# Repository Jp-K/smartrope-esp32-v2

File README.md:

# A-New-RoPE
Repository for testing the new version of RoPE's firmware

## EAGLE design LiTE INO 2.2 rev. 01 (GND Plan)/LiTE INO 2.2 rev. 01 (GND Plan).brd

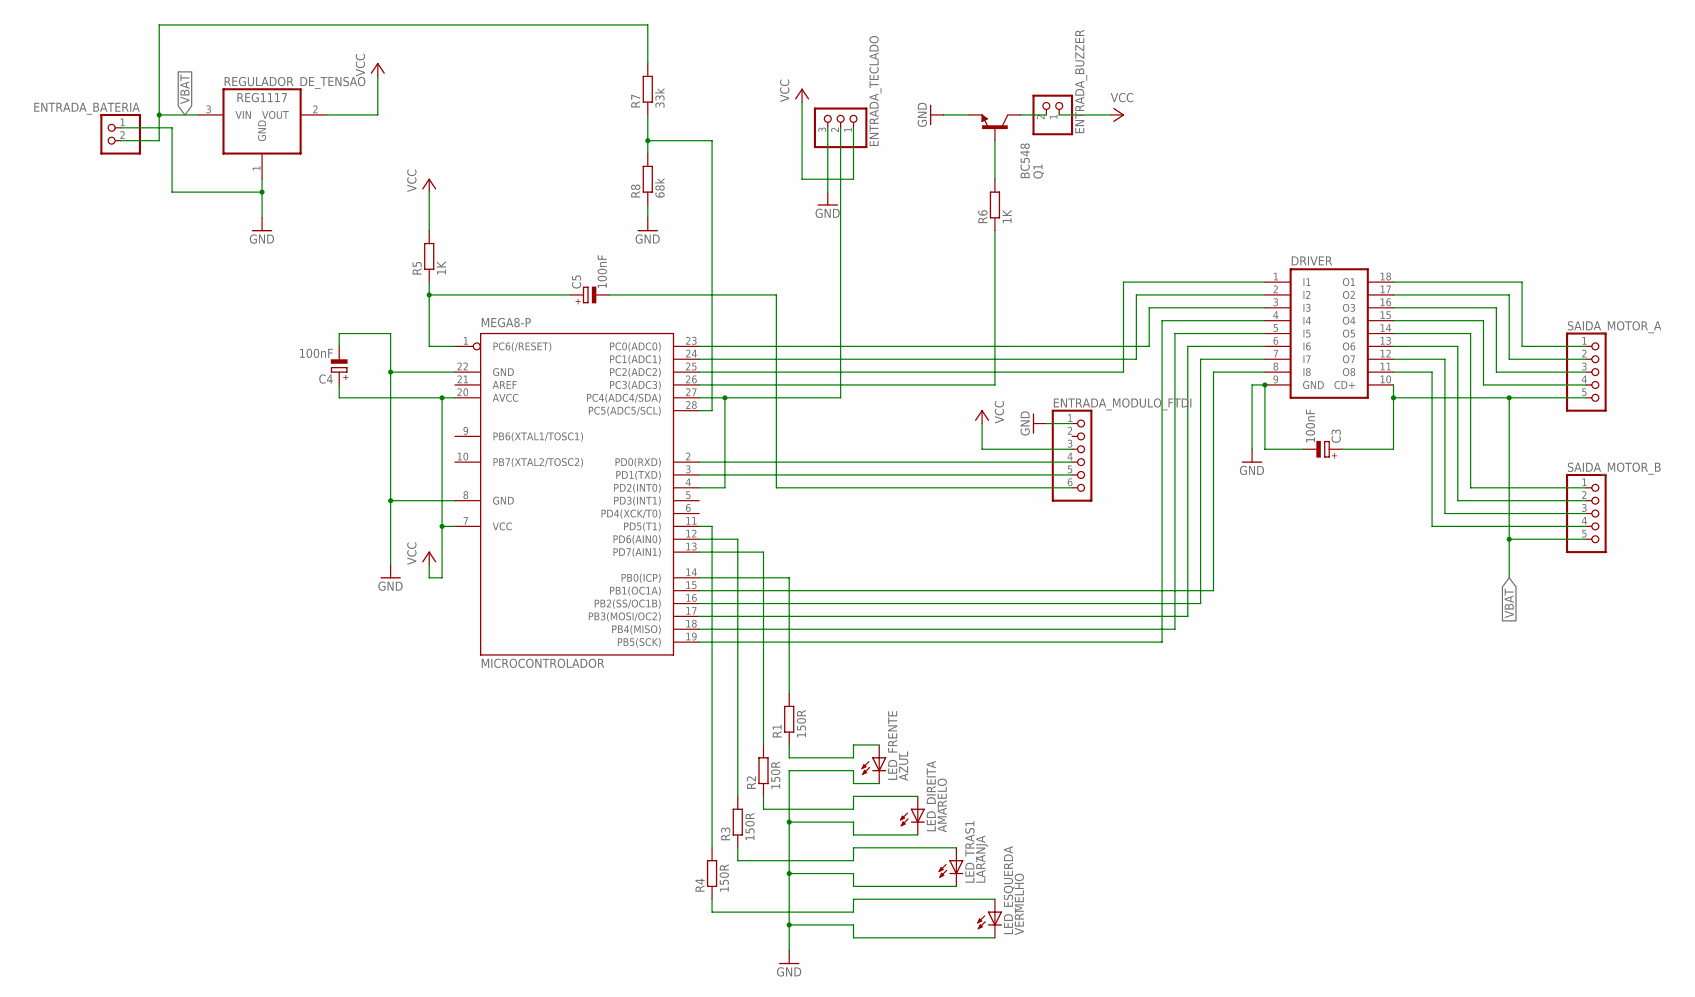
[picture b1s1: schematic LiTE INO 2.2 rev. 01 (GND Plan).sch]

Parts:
C3, C4, C5: 100nF; E5-5
DRIVER: ULN2803A; DIL18
ENTRADA_BATERIA: PINHD-1X2/90; 1X02/90
ENTRADA_BUZZER: PINHD-1X2/90; 1X02/90
ENTRADA_MODULO_FTDI: PINHD-1X6/90; 1X06/90
ENTRADA_TECLADO: PINHD-1X3/90; 1X03/90
LED_DIREITA: AMARELO; LED5MM
LED_ESQUERDA: VERMELHO; LED5MM
LED_FRENTE: AZUL; LED5MM
LED_TRAS1: LARANJA; LED5MM
MICROCONTROLADOR: MEGA8-P; DIL28-3
Q1: BC548; TO92-EBC
R1, R2, R3, R4: 150R; 0204/7
R5, R6: 1K; 0204/7
R7: 33k; 0204/7
R8: 68k; 0204/7
REGULADOR_DE_TENSAO: REG1117; SOT223
SAIDA_MOTOR_A: PINHD-1X5/90; 1X05/90
SAIDA_MOTOR_B: PINHD-1X5/90; 1X05/90

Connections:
GND: C3.-, C4.-, DRIVER.9 (GND), ENTRADA_BATERIA.1, ENTRADA_MODULO_FTDI.1, ENTRADA_TECLADO.3, LED_DIREITA.K (C), LED_ESQUERDA.K (C), LED_FRENTE.K (C), LED_TRAS1.K (C), MICROCONTROLADOR.8 (GND), MICROCONTROLADOR.22 (GND), Q1.E, R8.1, REGULADOR_DE_TENSAO.1 (GND)
unnamed: DRIVER.1 (I1), MICROCONTROLADOR.25 (PC2(ADC2))
unnamed: DRIVER.2 (I2), MICROCONTROLADOR.24 (PC1(ADC1))
unnamed: DRIVER.3 (I3), MICROCONTROLADOR.23 (PC0(ADC0))
unnamed: DRIVER.4 (I4), MICROCONTROLADOR.19 (PB5(SCK))
unnamed: DRIVER.5 (I5), MICROCONTROLADOR.18 (PB4(MISO))
unnamed: DRIVER.6 (I6), MICROCONTROLADOR.17 (PB3(MOSI/OC2))
unnamed: DRIVER.7 (I7), MICROCONTROLADOR.16 (PB2(SS/OC1B))
unnamed: DRIVER.8 (I8), MICROCONTROLADOR.15 (PB1(OC1A))
unnamed: LED_FRENTE.A, R1.1
unnamed: DRIVER.18 (O1), SAIDA_MOTOR_A.1
unnamed: DRIVER.17 (O2), SAIDA_MOTOR_A.2
unnamed: DRIVER.16 (O3), SAIDA_MOTOR_A.3
unnamed: DRIVER.15 (O4), SAIDA_MOTOR_A.4
unnamed: LED_DIREITA.A, R2.1
unnamed: DRIVER.14 (O5), SAIDA_MOTOR_B.1
unnamed: DRIVER.13 (O6), SAIDA_MOTOR_B.2
unnamed: DRIVER.12 (O7), SAIDA_MOTOR_B.3
unnamed: DRIVER.11 (O8), SAIDA_MOTOR_B.4
unnamed: LED_TRAS1.A, R3.1
unnamed: MICROCONTROLADOR.14 (PB0(ICP)), R1.2
unnamed: MICROCONTROLADOR.13 (PD7(AIN1)), R2.2
unnamed: MICROCONTROLADOR.12 (PD6(AIN0)), R3.2
unnamed: MICROCONTROLADOR.11 (PD5(T1)), R4.2
unnamed: ENTRADA_TECLADO.2, MICROCONTROLADOR.4 (PD2(INT0)), MICROCONTROLADOR.27 (PC4(ADC4/SDA))
unnamed: ENTRADA_BUZZER.2, Q1.C
unnamed: MICROCONTROLADOR.28 (PC5(ADC5/SCL)), R7.1, R8.2
unnamed: LED_ESQUERDA.A, R4.1
unnamed: MICROCONTROLADOR.26 (PC3(ADC3)), R6.1
unnamed: ENTRADA_MODULO_FTDI.4, MICROCONTROLADOR.2 (PD0(RXD))
unnamed: ENTRADA_MODULO_FTDI.5, MICROCONTROLADOR.3 (PD1(TXD))
unnamed: C5.-, ENTRADA_MODULO_FTDI.6
unnamed: C5.+, MICROCONTROLADOR.1 (PC6(/RESET)), R5.1
unnamed: Q1.B, R6.2
VBAT: C3.+, DRIVER.10 (CD+), ENTRADA_BATERIA.2, R7.2, REGULADOR_DE_TENSAO.3 (VIN), SAIDA_MOTOR_A.5, SAIDA_MOTOR_B.5
VCC: C4.+, ENTRADA_BUZZER.1, ENTRADA_MODULO_FTDI.3, ENTRADA_TECLADO.1, MICROCONTROLADOR.7 (VCC), MICROCONTROLADOR.20 (AVCC), R5.2, REGULADOR_DE_TENSAO.2 (VOUT)

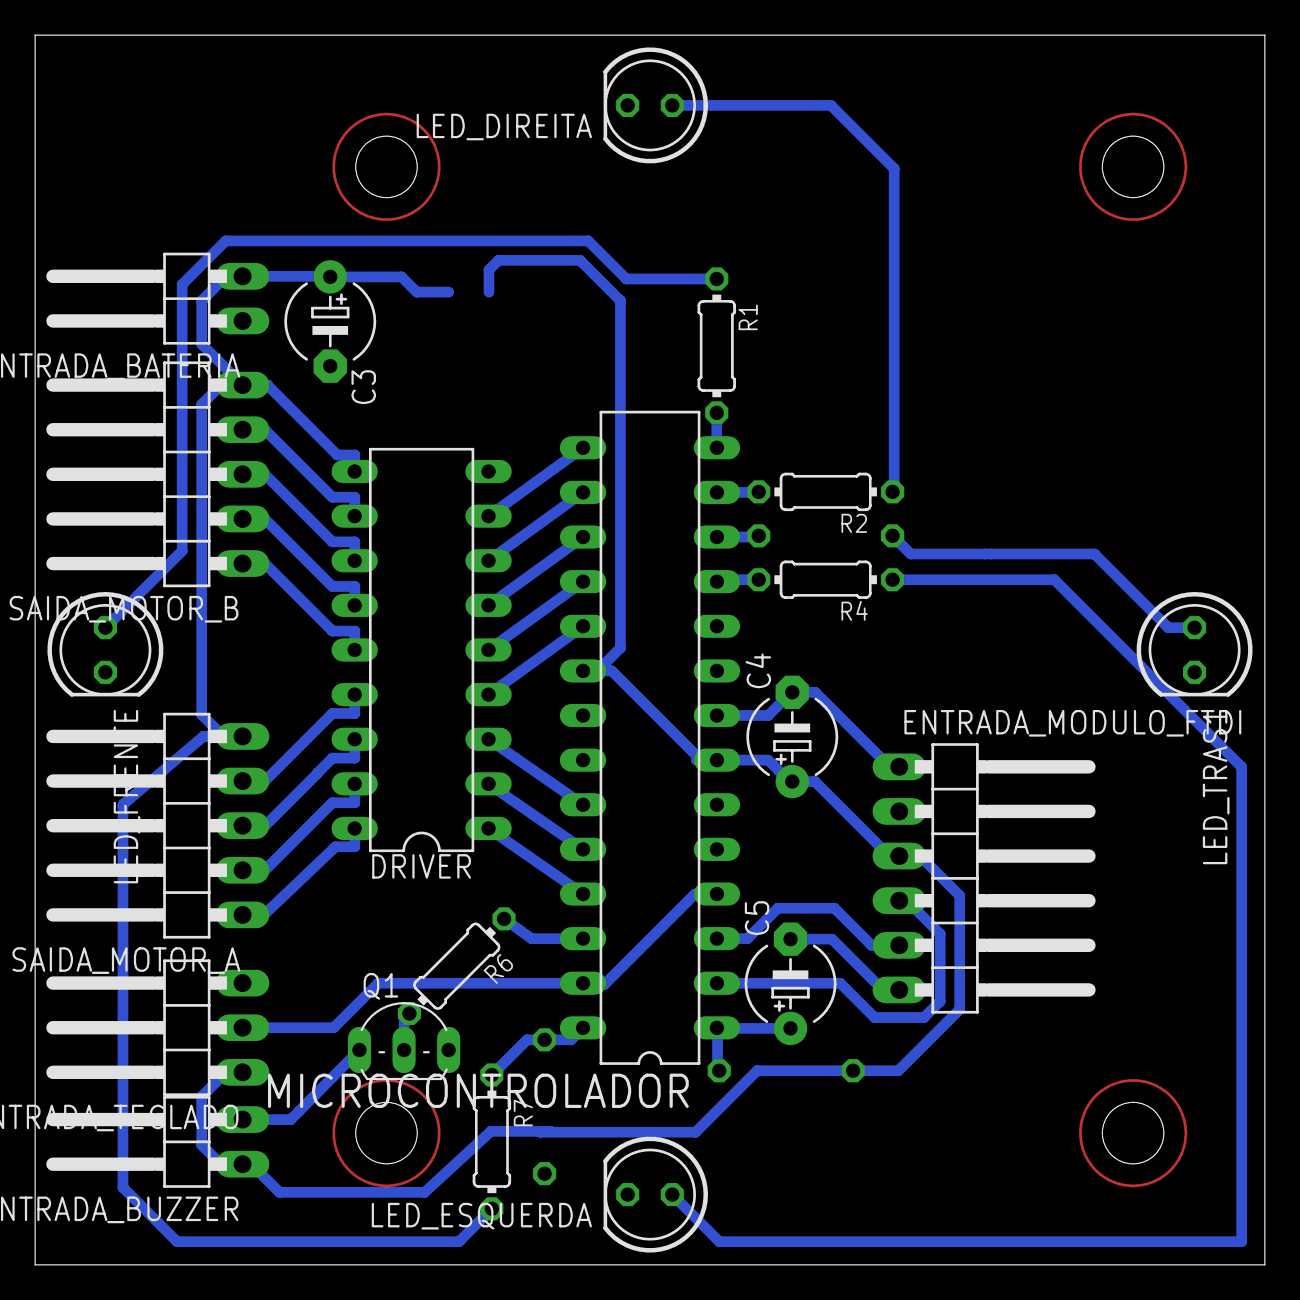
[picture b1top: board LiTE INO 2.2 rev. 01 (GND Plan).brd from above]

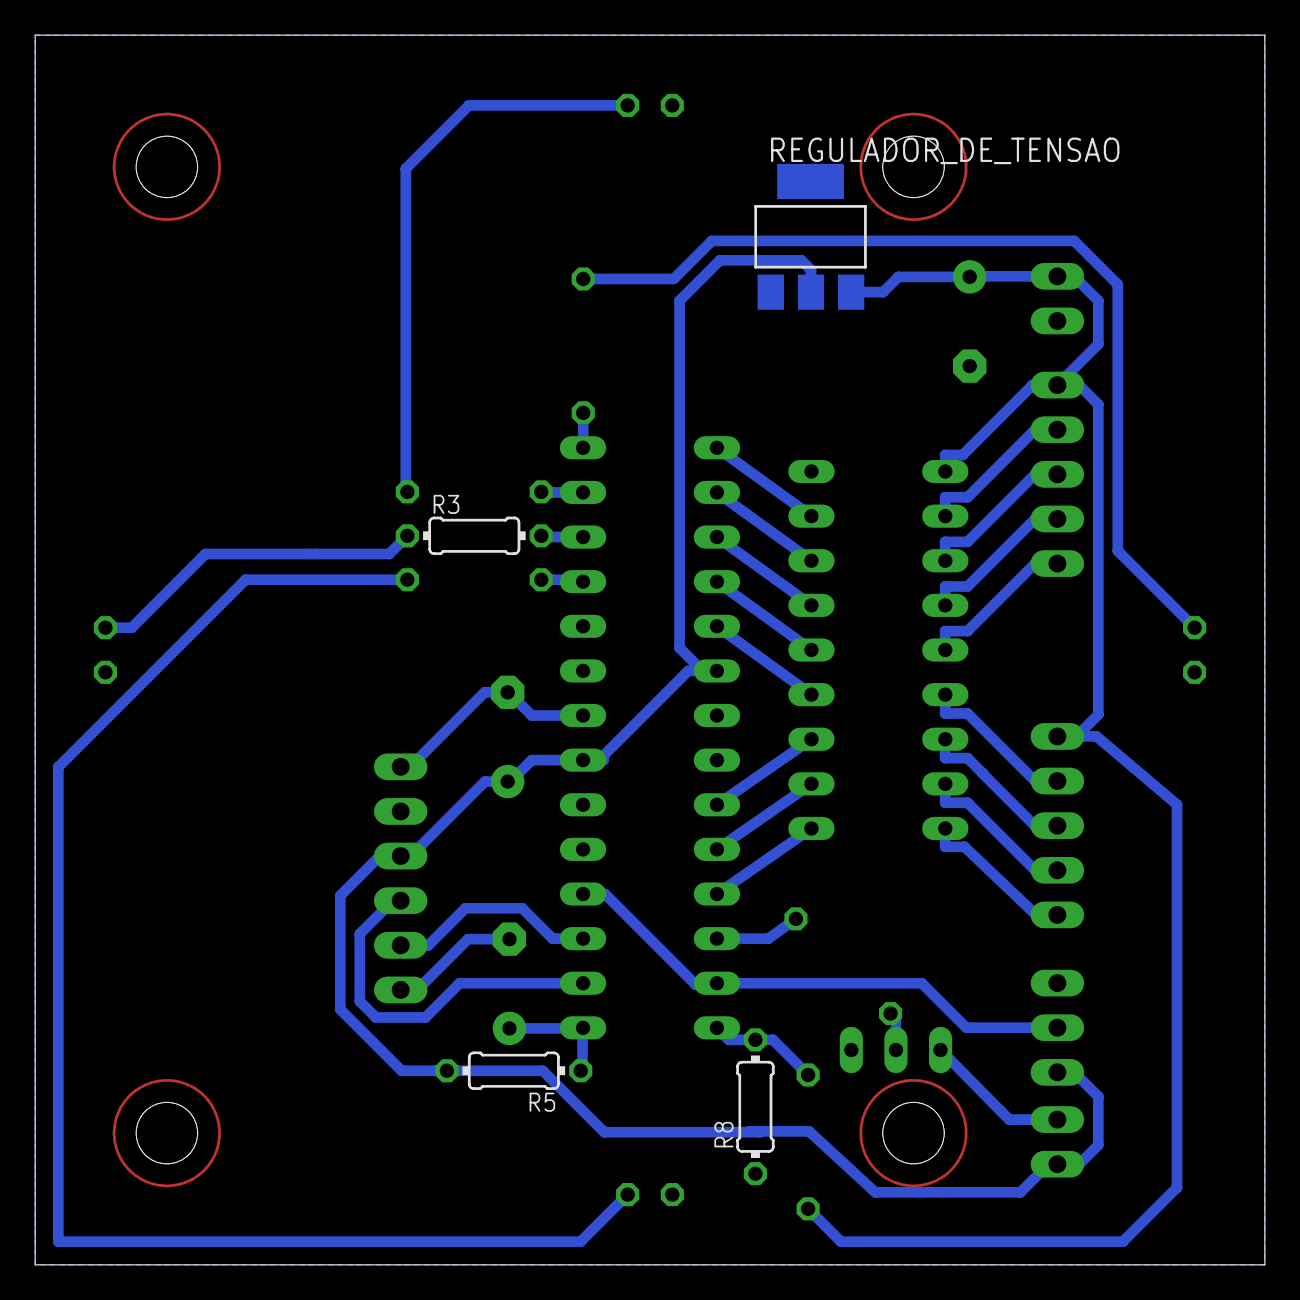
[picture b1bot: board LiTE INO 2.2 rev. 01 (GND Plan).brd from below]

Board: 2 copper layers, 70.0 x 70.0 mm, 25 parts (4 on the bottom side), 36 nets.

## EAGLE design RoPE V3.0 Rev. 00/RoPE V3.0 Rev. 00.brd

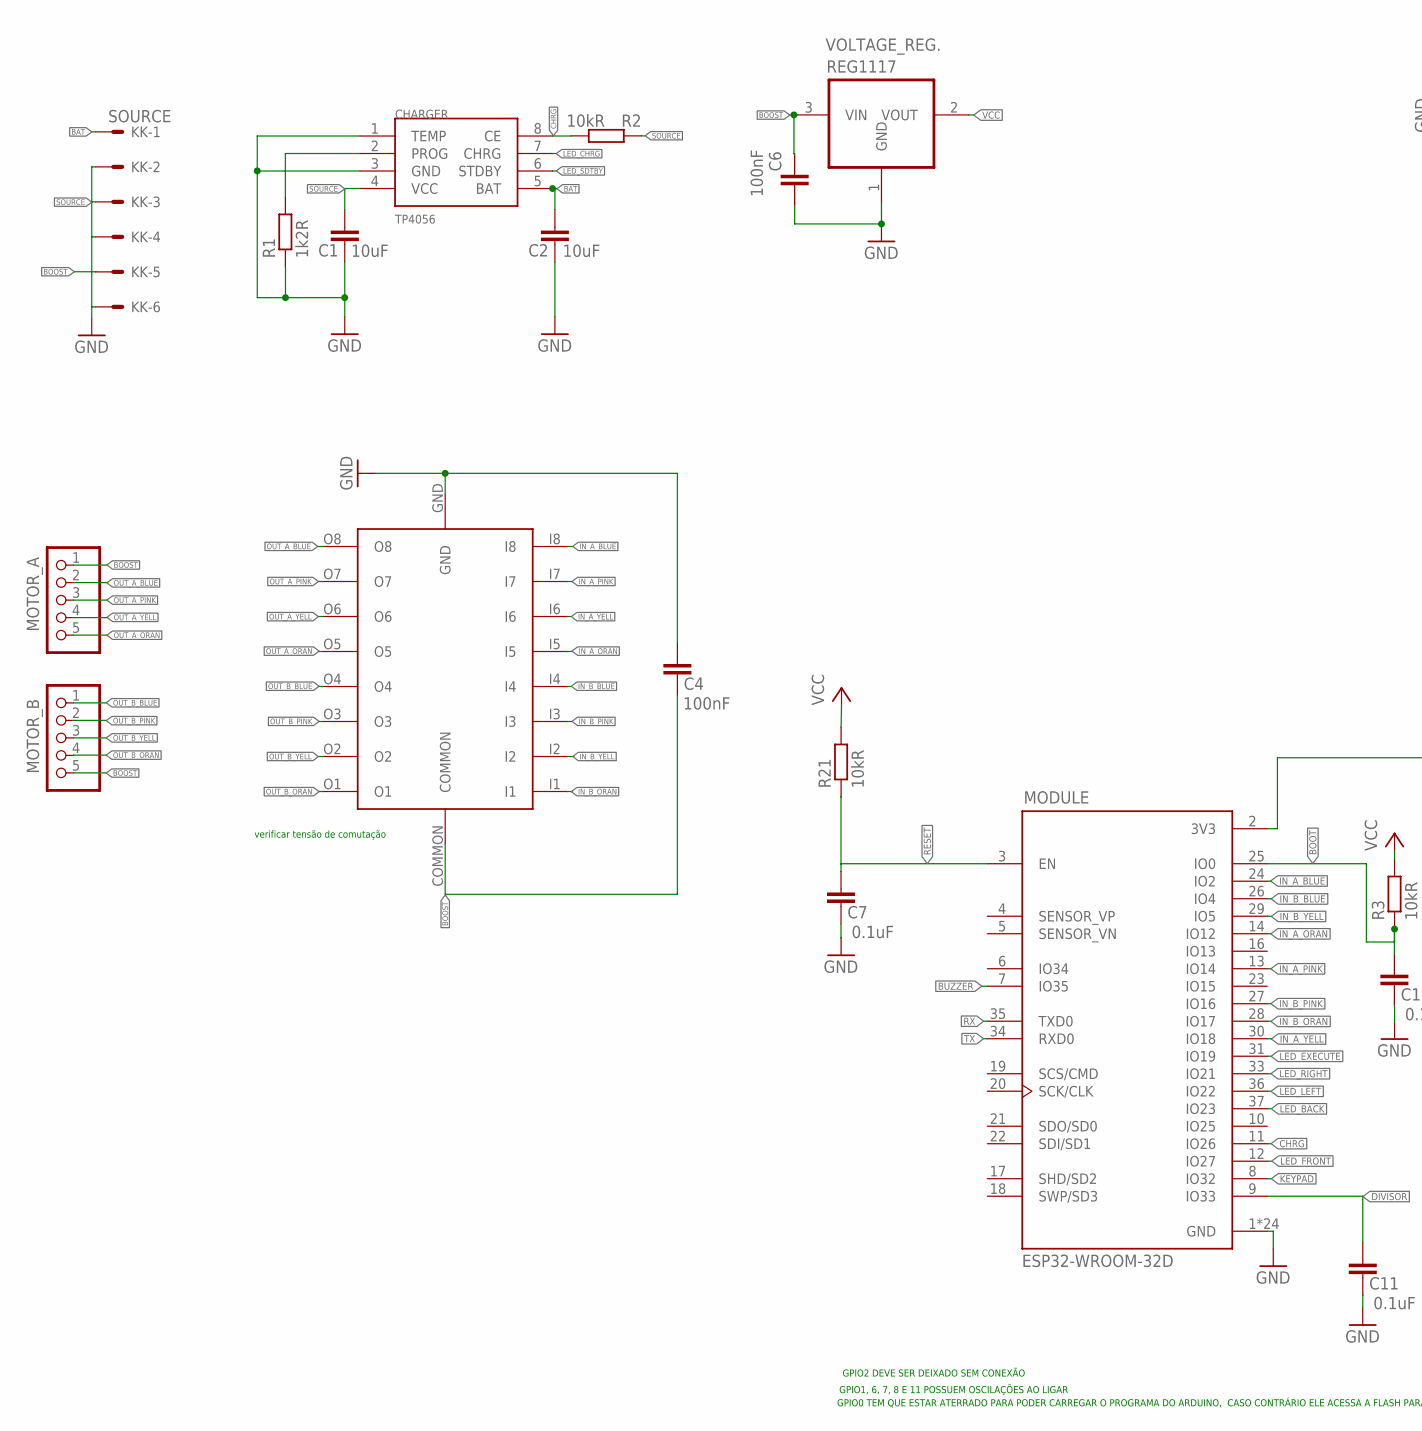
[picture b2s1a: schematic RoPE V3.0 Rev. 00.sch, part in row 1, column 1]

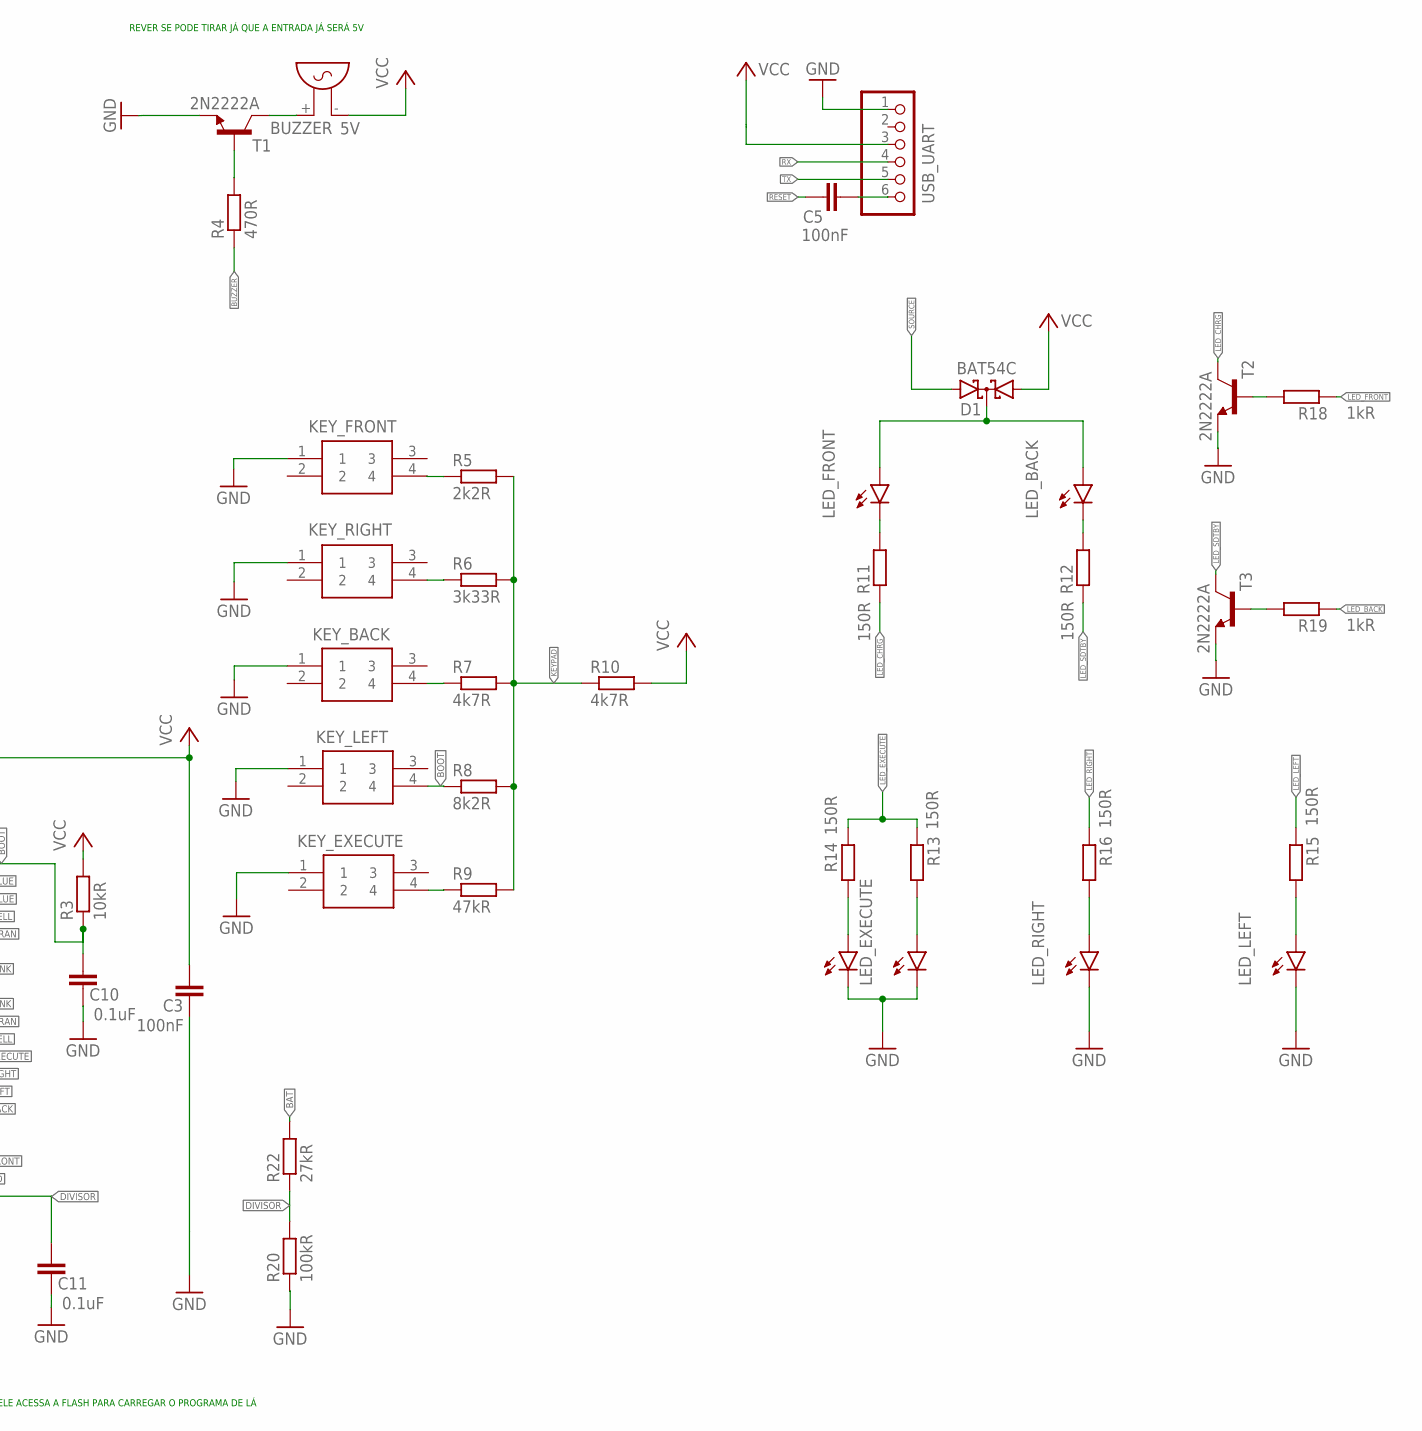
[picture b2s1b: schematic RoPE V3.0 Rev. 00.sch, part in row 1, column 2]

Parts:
BUZZER: 5V; F/QMX
C1, C2: 10uF; C1210
C3, C4, C5, C6: 100nF; C1210
C7, C10, C11: 0.1uF; C1210
CHARGER: TP4056; SOP-8
D1: BAT54C; SOT23
DRIVER: ULN2803AFWG
KEY_BACK: B3F-4050; B3F-4000
KEY_EXECUTE: B3F-4050; B3F-4000
KEY_FRONT: B3F-4050; B3F-4000
KEY_LEFT: B3F-4050; B3F-4000
KEY_RIGHT: B3F-4050; B3F-4000
KK: SOURCE; 7395-06
LED_BACK: ORANGE; KA-3528ASYC
LED_EXECUTE, LED_EXECUTE2: GREEN; KA-3528ASYC
LED_FRONT: BLUE; KA-3528ASYC
LED_LEFT: RED; KA-3528ASYC
LED_RIGHT: RED; KA-3528ASYC
MODULE: ESP32-WROOM-32D; MODULE_ESP32-WROOM-32D
MOTOR_A: PINHD-1X5/90; 1X05/90
MOTOR_B: PINHD-1X5/90; 1X05/90
R1: 1k2R; R1206W
R2, R3, R21: 10kR; R1206W
R4: 470R; R1206W
R5: 2k2R; R1206W
R6: 3k33R; R1206W
R7, R10: 4k7R; R1206W
R8: 8k2R; R1206W
R9: 47kR; R1206W
R11, R12, R13, R14, R15, R16: 150R; R1206W
R18, R19: 1kR; R1206W
R20: 100kR; R1206W
R22: 27kR; R1206W
T1, T2, T3: 2N2222A; SOT23-BEC
USB_UART: PINHD-1X6/90; 1X06/90
VOLTAGE_REG.: REG1117; SOT223

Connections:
BAT: C2.2, CHARGER.5 (BAT), KK.1, R22.2
BOOST: C4.1, C6.2, DRIVER.COMMON, KK.5, MOTOR_A.1, MOTOR_B.5, VOLTAGE_REG..3 (VIN)
BOOT: C10.2, KEY_LEFT.4, MODULE.25 (IO0), R3.1, R8.1
BUZZER: MODULE.7 (IO35), R4.1
CHRG: CHARGER.8 (CE), MODULE.11 (IO26), R2.2
DIVISOR: C11.2, MODULE.9 (IO33), R20.2, R22.1
GND: C1.1, C2.1, C3.1, C4.2, C6.1, C7.1, C10.1, C11.1, CHARGER.1 (TEMP), CHARGER.3 (GND), DRIVER.GND, KEY_BACK.1, KEY_EXECUTE.1, KEY_FRONT.1, KEY_LEFT.1, KEY_RIGHT.1, KK.2, KK.4, KK.6, LED_EXECUTE.C, LED_EXECUTE2.C, LED_LEFT.C, LED_RIGHT.C, MODULE.1 (GND), MODULE.15 (GND), MODULE.38 (GND), MODULE.39_1 (GND), MODULE.39_2 (GND), MODULE.39_3 (GND), MODULE.39_4 (GND), MODULE.39_5 (GND), MODULE.39_6 (GND), MODULE.39_7 (GND), MODULE.39_8 (GND), MODULE.39_9 (GND), MODULE.39_10 (GND), MODULE.39_11 (GND), MODULE.39_12 (GND), MODULE.39_13 (GND), MODULE.39_14 (GND), MODULE.39_15 (GND), MODULE.39_16 (GND), MODULE.39_17 (GND), MODULE.39_18 (GND), MODULE.39_19 (GND), MODULE.39_20 (GND), MODULE.39_21 (GND), R1.1, R20.1, T1.E, T2.E, T3.E, USB_UART.1, VOLTAGE_REG..1 (GND)
IN_A_BLUE: DRIVER.I8, MODULE.24 (IO2)
IN_A_ORAN: DRIVER.I5, MODULE.14 (IO12)
IN_A_PINK: DRIVER.I7, MODULE.13 (IO14)
IN_A_YELL: DRIVER.I6, MODULE.30 (IO18)
IN_B_BLUE: DRIVER.I4, MODULE.26 (IO4)
IN_B_ORAN: DRIVER.I1, MODULE.28 (IO17)
IN_B_PINK: DRIVER.I3, MODULE.27 (IO16)
IN_B_YELL: DRIVER.I2, MODULE.29 (IO5)
KEYPAD: MODULE.8 (IO32), R5.2, R6.2, R7.2, R8.2, R9.2, R10.1
LED_BACK: MODULE.37 (IO23), R19.1
LED_CHRG: CHARGER.7 (CHRG), R11.1, T2.C
LED_EXECUTE: MODULE.31 (IO19), R13.1, R14.1
LED_FRONT: MODULE.12 (IO27), R18.1
LED_LEFT: MODULE.36 (IO22), R15.1
LED_RIGHT: MODULE.33 (IO21), R16.1
LED_SDTBY: CHARGER.6 (STDBY), R12.1, T3.C
unnamed: C5.1, USB_UART.6
unnamed: KEY_RIGHT.4, R6.1
unnamed: LED_BACK.C, R12.2
unnamed: KEY_FRONT.4, R5.1
unnamed: BUZZER.+ (2), T1.C
unnamed: R4.2, T1.B
unnamed: LED_FRONT.C, R11.2
unnamed: LED_EXECUTE.A, R13.2
unnamed: LED_EXECUTE2.A, R14.2
unnamed: LED_RIGHT.A, R16.2
unnamed: LED_LEFT.A, R15.2
unnamed: CHARGER.2 (PROG), R1.2
unnamed: KEY_BACK.4, R7.1
unnamed: R19.2, T3.B
unnamed: R18.2, T2.B
unnamed: D1.3 (CC), LED_BACK.A, LED_FRONT.A
unnamed: KEY_EXECUTE.4, R9.1
OUT_A_BLUE: DRIVER.O8, MOTOR_A.2
OUT_A_ORAN: DRIVER.O5, MOTOR_A.5
OUT_A_PINK: DRIVER.O7, MOTOR_A.3
OUT_A_YELL: DRIVER.O6, MOTOR_A.4
OUT_B_BLUE: DRIVER.O4, MOTOR_B.1
OUT_B_ORAN: DRIVER.O1, MOTOR_B.4
OUT_B_PINK: DRIVER.O3, MOTOR_B.2
OUT_B_YELL: DRIVER.O2, MOTOR_B.3
RESET: C5.2, C7.2, MODULE.3 (EN), R21.1
RX: MODULE.35 (TXD0), USB_UART.4
SOURCE: C1.2, CHARGER.4 (VCC), D1.2 (A2), KK.3, R2.1
TX: MODULE.34 (RXD0), USB_UART.5
VCC: BUZZER.- (1), C3.2, D1.1 (A1), MODULE.2 (3V3), R3.2, R10.2, R21.2, USB_UART.3, VOLTAGE_REG..2 (VOUT)

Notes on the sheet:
GPIO0 TEM QUE ESTAR ATERRADO PARA PODER CARREGAR O PROGRAMA DO ARDUINO, CASO CONTRÁRIO ELE ACESSA A FLASH PARA CARREGAR O PROGRAMA DE LÁ
GPIO2 DEVE SER DEIXADO SEM CONEXÃO
GPIO1, 6, 7, 8 E 11 POSSUEM OSCILAÇÕES AO LIGAR
REVER SE PODE TIRAR JÁ QUE A ENTRADA JÁ SERÁ 5V
verificar tensão de comutação

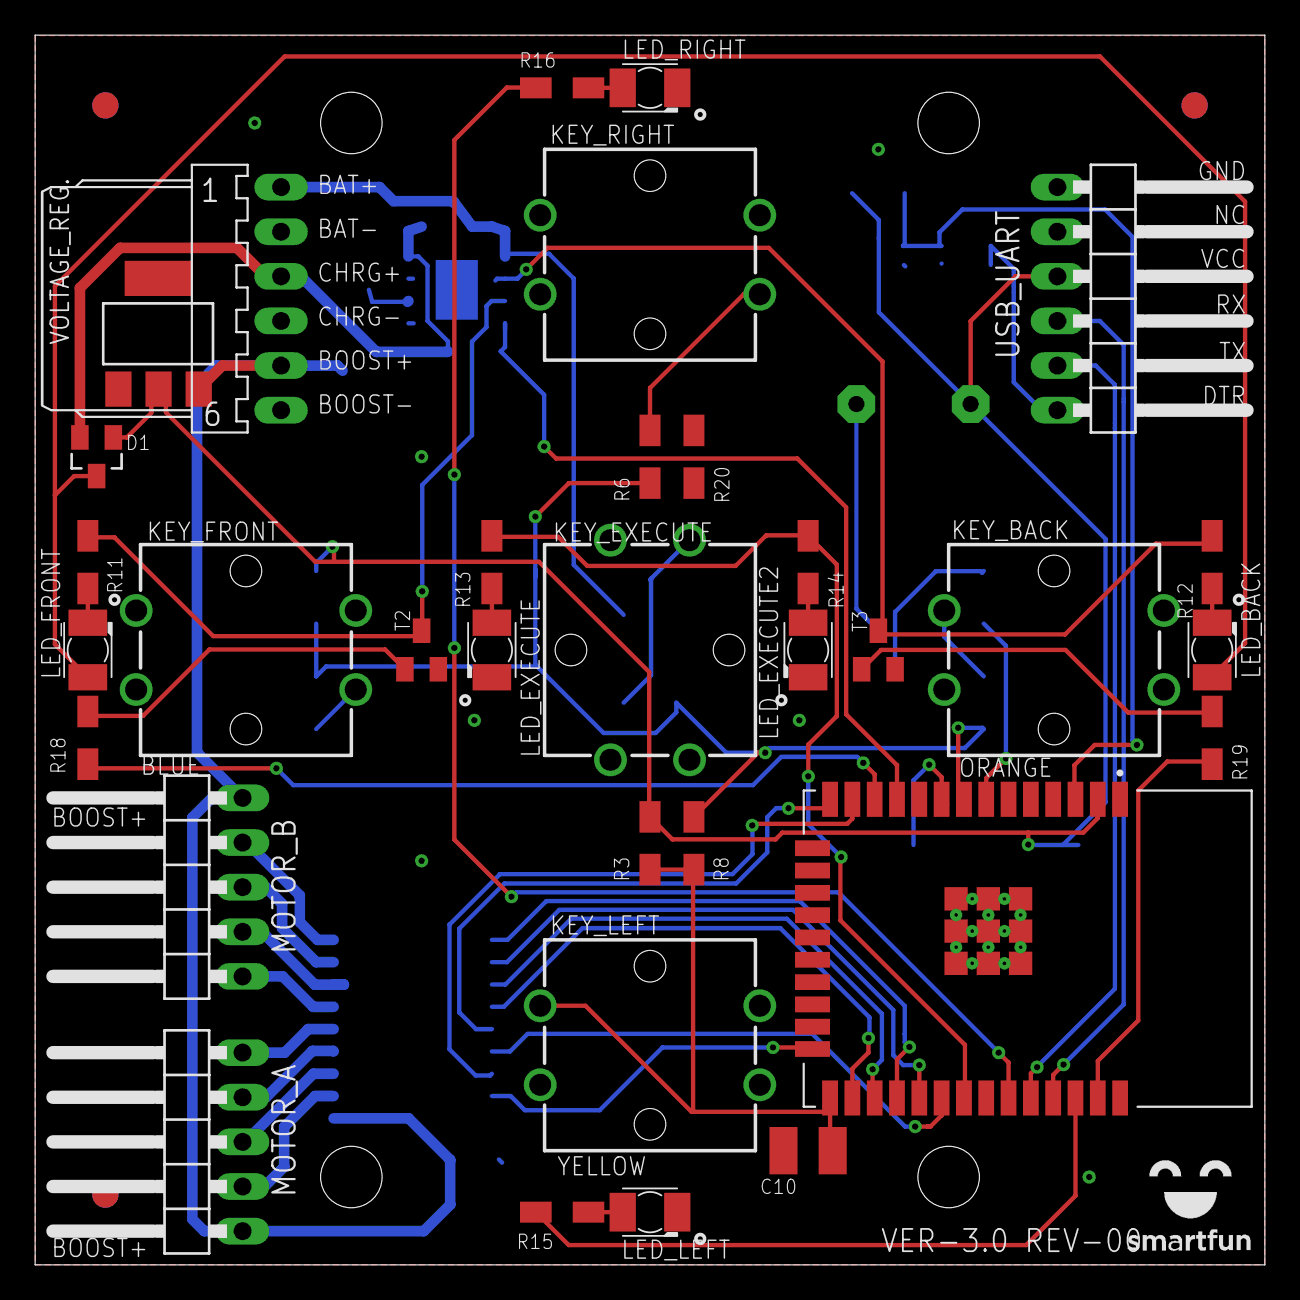
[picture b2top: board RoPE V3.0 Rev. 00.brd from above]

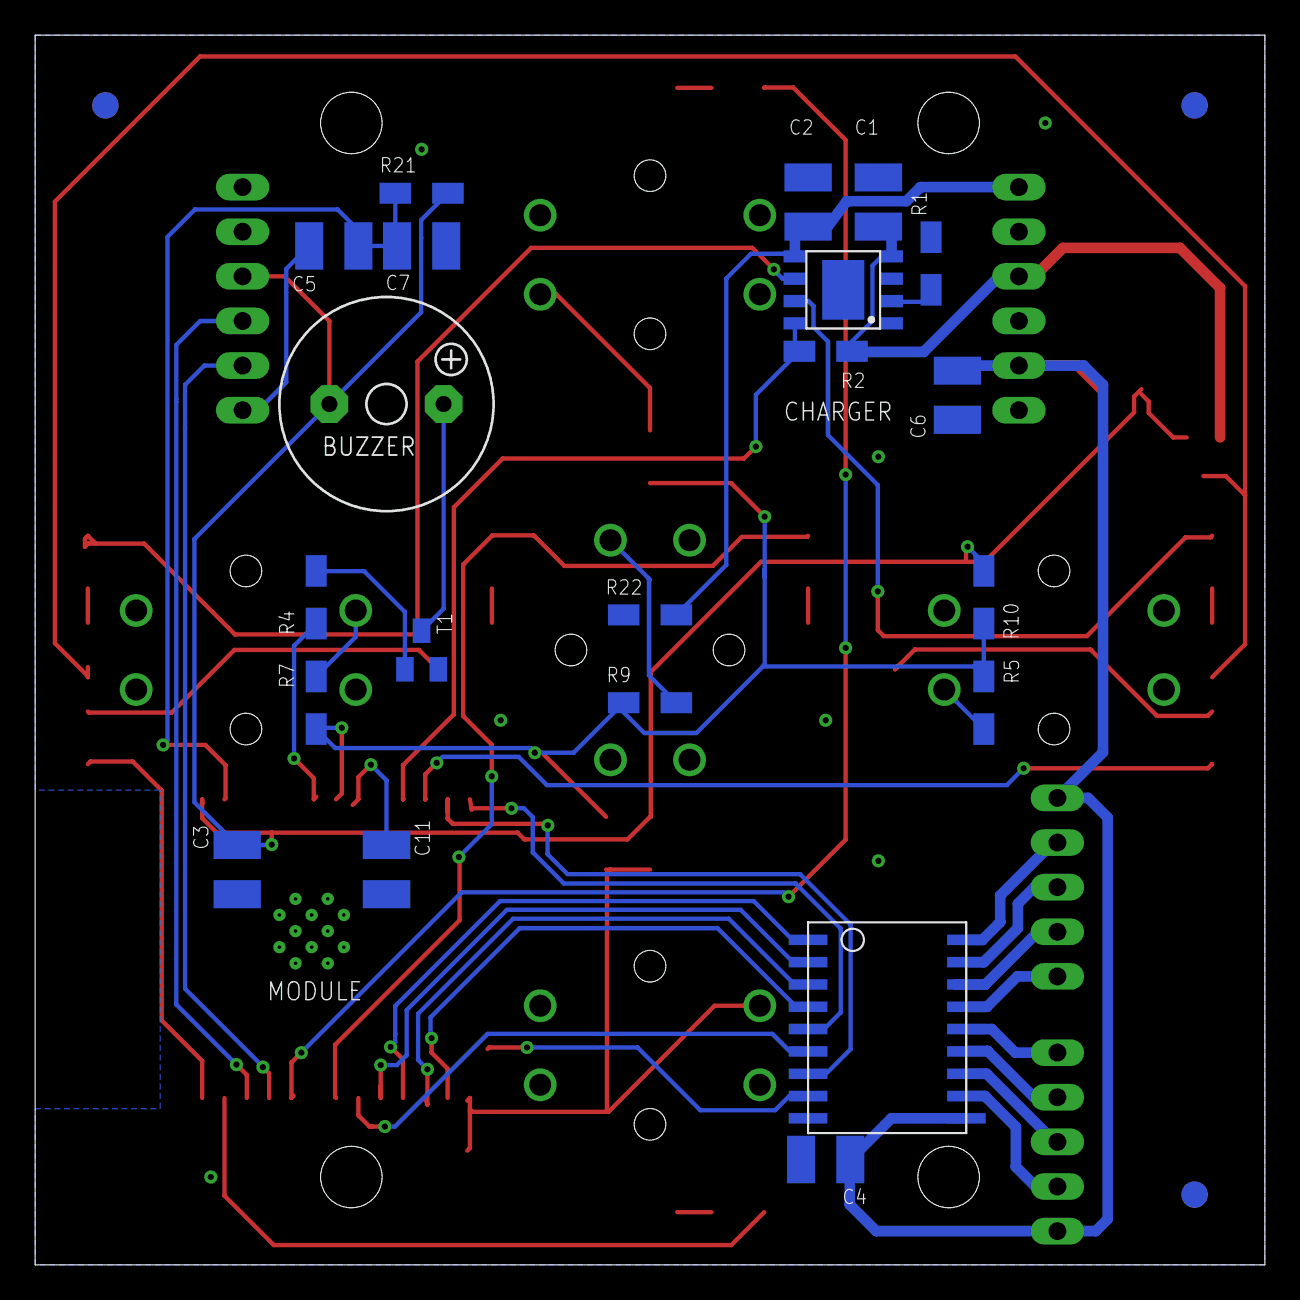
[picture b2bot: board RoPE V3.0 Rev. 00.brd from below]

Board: 2 copper layers, 70.0 x 70.0 mm, 60 parts (24 on the bottom side), 53 nets.

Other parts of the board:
U$1, U$2, U$3, U$4, U$5, U$6: FIDUCIAL_G15

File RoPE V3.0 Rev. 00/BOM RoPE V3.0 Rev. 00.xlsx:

| COMPONENT | QUANTITY | PART NUMBER | PROJECT REFERENCE
 | Barra de Pinos 1x6x(17mm) 90º | 1 | 68015-406HLF | USB_SERIAL
 | Barra de Pinos 1x5x(17mm) 90º | 2 | 68015-405HLF | MOTOR_A, MOTOR_B, SPI
 | Buzzer Passivo | 1 | EET1290-12O-2.4-140-6.5-R-LAB | BUZZER;
 | Capa para Chave Táctil Amarela | 1 | B32-1330 | KEY_RIGHT;
 | Capa para Chave Táctil Azul | 1 | B32-1340 | KEY_FRONT;
 | Capa para Chave Táctil Laranja | 1 | B32-1320 | KEY_BACK;
 | Capa para Chave Táctil Verde | 1 | B32-1350 | KEY_EXECUTE;
 | Capa para Chave Táctil Vermelha | 1 | B32-1380 | KEY_LEFT;
 | Capacitor 100nF 25V/50V | 3 | C1210C104K5RACTU | C3; C4; C5;
 | Capacitor 10uF 25V/50V | 2 | C1210C106K6PAC7800 | C1; C2;
 | Capacitor 0,1uF 25V/50V | 3 | C1210C104J1GAC7800 | C7; C10; C11
 | Chave Táctil 12X12mm | 5 | B3F-4050 | KEY_FRONT; KEY_BACK; KEY_LEFT; KEY_RIGHT; KEY_EXECUTE;
 | Chip de Carregamento | 1 | TP4056-42-SOP8-PP | CHARGER;
 | Conector KK 1x6 90º | 1 | PCMN2-06 | SOURCE
 | Diodo Schottky | 2 | BAT54CLT1G | D1
 | Driver dos Motores | 1 | ULN2803AFWG | DRIVER;
 | LED Branco 3V 40 mA | 6 | GW JTLMS1.EM-GVH2-XX55-1-60-R18 | LED_FRONT; LED_BACK; LED_LEFT; LED_RIGHT; LED_EXECUTE; LED_EXECUTE2;
 | Microcontrolador | 1 | ESP32-WROOM-32D | MPU
 | Regulador de Tensão 5V | 1 | LM1117MPX-5.0 | VOLTAGE_REG.
 | Resistor 27kR 5% 1/4W | 1 | CR1206-JW-273ELF | R20
 | Resistor 100kR 5% 1/4W | 1 | CR1206-JW-104ELF | R20
 | Resistor 10kR 5% 1/4W | 3 | CR1206-JW-103ELF | R2; R3; R21
 | Resistor 150R 5% 1/4W | 6 | CR1206-JW-151ELF | R11, R12, R13, R14, R15, R16
 | Resistor 1k2R 5% 1/4W | 1 | AR1206JR-071K2L | R1;
 | Resistor 1k5R 5% 1/4W | 1 | AR1206JR-071K5L | R6;
 | Resistor 1kR 5% 1/4W | 2 | AR1206JR-071KL | R18, R19
 | Resistor 2k2R 5% 1/4W | 1 | AR1206JR-072K2L | R5;
 | Resistor 3k3R 5% 1/4W | 1 | AR1206JR-073K3L | R6;
 | Resistor 470R 5% 1/4W | 1 | AR1206JR-07470RL | R4
 | Resistor 4k7R 5% 1/4W | 2 | CR1206-JW-472GLF | R7; R10;
 | Resistor 47kR 5% 1/4W | 1 | CR1206-FX-4702ELF | R9
 | Resistor 8k2R 5% 1/4W | 1 | CRM1206-FX-8201ELF | R8
 | Transistor NPN | 3 | 2N2222AUA | T1, T2, T3

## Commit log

2024-12-09 init
2024-12-09 unitparams
2024-12-09 params

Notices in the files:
parts and their libraries:
dicons: Copyright (C) 2004, Bob Starr (rtzaudio@mindspring.com)
